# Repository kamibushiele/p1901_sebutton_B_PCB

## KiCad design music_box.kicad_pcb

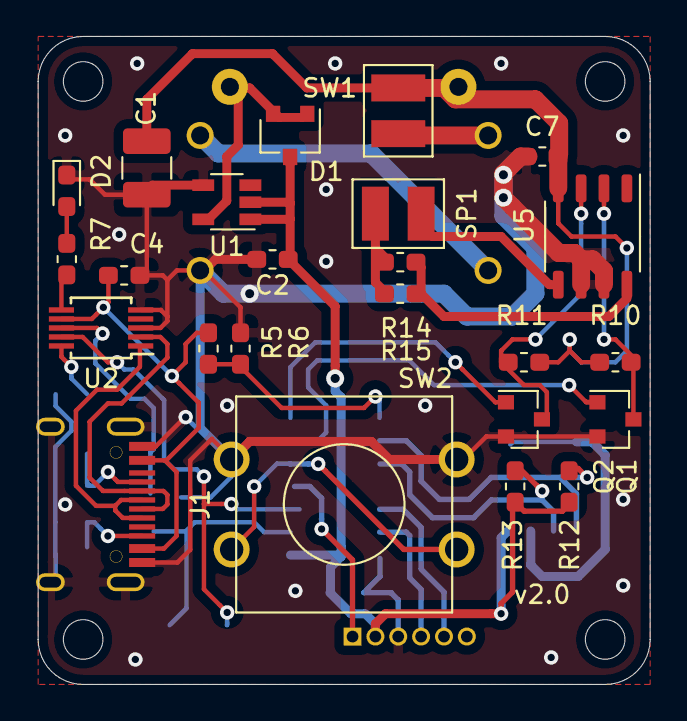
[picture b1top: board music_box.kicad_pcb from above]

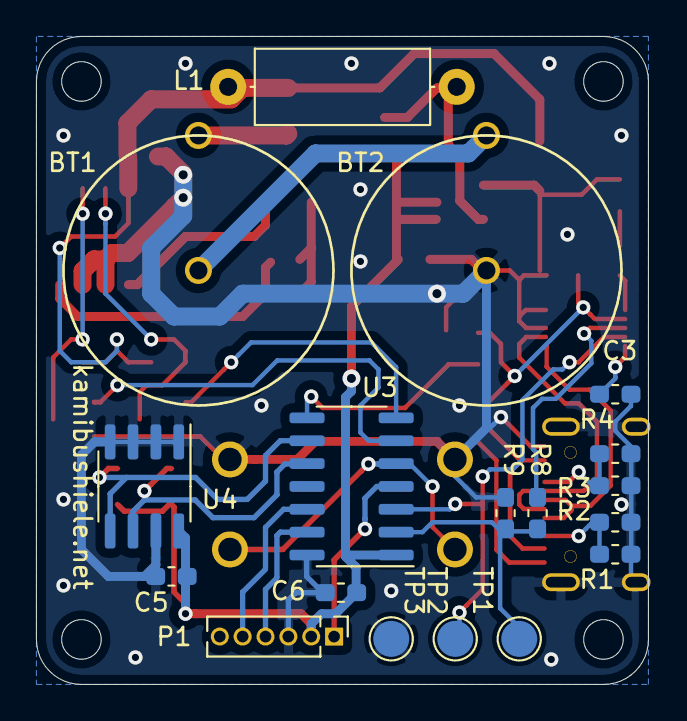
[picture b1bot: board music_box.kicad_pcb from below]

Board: 2 copper layers, 34.0 x 36.0 mm, 46 parts (18 on the bottom side), 31 nets.

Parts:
BT1, BT2: Battery_Cell; CH23-1225
C1: 47u; C_1210_3225Metric_Pad1.42x2.65mm_HandSolder
C2: 22u; C_0603_1608Metric_Pad1.05x0.95mm_HandSolder
C3, C4, C5, C6, C7: 0.1u 1608; C_0603_1608Metric_Pad1.05x0.95mm_HandSolder
D1: RB411D; SC-59
D2: LED NC; D_0603_1608Metric_Pad1.05x0.95mm_HandSolder
H1, H2, H3, H4: MountingHole; M2-drillHole_nosilk_nopad
J1: USB_C_Receptacle; USB_C_01
L1: 100uH; L_Axial_L9.5mm_D4.0mm_P12.70mm_Horizontal_Fastron_SMCC
P1: ICSPforPICKit; PinHeader_1x06_P1.27mm_Vertical
Q1, Q2: 2n7002; SOT-23
R1, R2, R3, R4, R5, R6, R8, R9, R10, R11, R12, R13: 10k; R_0603_1608Metric_Pad1.05x0.95mm_HandSolder
R7: 470 NC; R_0603_1608Metric_Pad1.05x0.95mm_HandSolder
R14, R15: 47; R_0603_1608Metric_Pad1.05x0.95mm_HandSolder
SP1: sp; 2.54-2pin-lay
SW1: POWER; 2.54-2pin-lay
SW2: SW_Push; TVGP01-G73BB
TP1: tp_PC2MC; TestPoint_Pad_D2.0mm
TP2: tp_MC2PC; TestPoint_Pad_D2.0mm
TP3: tp_GND; TestPoint_Pad_D2.0mm
U1: HT77XXA_SOT-25; TSOT-23-5
U2: CH340E; MSOP-10_3x3mm_P0.5mm
U3: PIC16(L)F18324; SOIC-14_3.9x8.7mm_P1.27mm
U4: 24FC256; SOIC-8_3.9x4.9mm_P1.27mm
U5: TC118SS; SSOP-8_3.9x5.05mm_P1.27mm

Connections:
+3V3: C2.1, C5.1, C6.1, D1.3, P1.2, R12.1, R13.1, U1.1, U1.2, U3.1, U4.8
+5V: C4.1, J1.A4, R5.1, U2.7
+BATT: C1.1, C7.1, L1.1, R10.1, R11.1, SW1.2, U5.4
/ConnectUSB: R5.2, R6.1, U3.8
/D+: J1.A6, J1.B6, U2.1
/D-: J1.A7, J1.B7, U2.2
/PIC_ICSP_CLK: P1.5, U3.12
/PIC_ICSP_DAT: P1.4, U3.13
/PIC_MCLR: P1.1, U3.4
/SCL: R13.2, U3.10, U4.6
/SDA: R12.2, U3.9, U4.5
/SPD1: Q1.1, U3.6
/SPD1_1: Q1.3, R10.2, U5.2
/SPD2: Q2.1, U3.7
/SPD2_1: Q2.3, R11.2, U5.3
/SW: SW2.2, U3.5
/UART_MC2PC: TP2.1, U2.9, U3.3
/UART_PC2MC: R8.2, R9.1, TP1.1, U3.2
GND: BT2.2, C1.2, C2.2, C3.2, C4.2, C5.2, C6.2, C7.2, D2.1, J1.A1, J1.S1, P1.3, Q1.2, Q2.2, R1.2, R2.2, R3.2, R4.2, R6.2, R9.2, SW2.1, TP3.1, U1.4, U2.3, U2.5, U3.14, U4.1, U4.2, U4.3, U4.4, U4.7, U5.6, U5.7
unnamed: BT1.1, SW1.1
unnamed: BT1.2, BT2.1
unnamed: C3.1, U2.10
unnamed: D1.1, D1.2, L1.2, U1.5
unnamed: D2.2, R7.2
unnamed: J1.A5, R3.1, R4.1
unnamed: J1.B5, R1.1, R2.1
unnamed: R7.1, U2.6
unnamed: R8.1, U2.8
unnamed: R14.1, R15.1, U5.8
unnamed: R14.2, R15.2, SP1.1
unnamed: SP1.2, U5.5

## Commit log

2022-02-13 ver2
2022-02-13 pdf追跡除外
